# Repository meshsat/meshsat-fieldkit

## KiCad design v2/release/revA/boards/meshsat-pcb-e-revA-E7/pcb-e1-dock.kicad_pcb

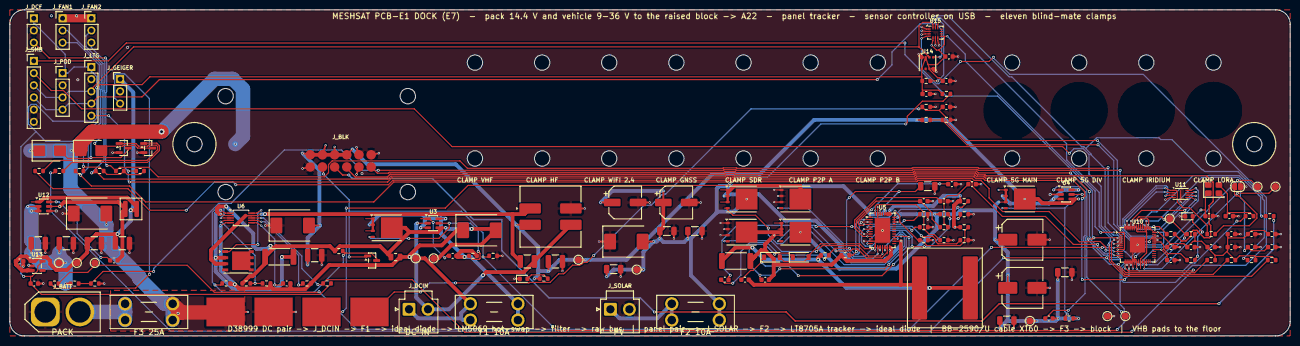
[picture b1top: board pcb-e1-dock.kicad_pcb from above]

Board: 4 copper layers, 267.0 x 68.0 mm, 189 parts (0 on the bottom side), 94 nets.

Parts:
C1, C31: 10u 25V 1210; C_1210_3225Metric
C2: 100n 100V; C_0805_2012Metric
C4, C28: 100n 50V; C_0603_1608Metric
C5: 100n (TIMER); C_0603_1608Metric
C6: 1u 100V 1210 (X, input side); C_1210_3225Metric
C7: 1u 100V 1210 (X, bus side); C_1210_3225Metric
C8: 10u 50V 1210; C_1210_3225Metric
C11, C12: 100u 35V Panasonic EEHZK1V101XP hybrid polymer (7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; CP_Elec_6.3x7.7
C13, C14: 10u 50V; C_1206_3216Metric
C15: 4.7u 50V; C_1206_3216Metric
C16: 1n; C_0603_1608Metric
C17, C18: 470n 25V; C_0603_1608Metric
C19: 4.7u 25V; C_1206_3216Metric
C20, C34, C35, C45, C46, C47: 1u; C_0603_1608Metric
C21: 4.7n; C_0603_1608Metric
C22: 100p; C_0603_1608Metric
C23, C30, C38, C39, C40, C41, C42, C43, C44, C48, C49, C50, C51: 100n; C_0603_1608Metric
C24, C25: 39u 35V Panasonic 35SVPF39M polymer (6.9 mm); CP_Elec_8x6.7
C26, C27: 10u 25V; C_1206_3216Metric
C32, C33: 22u 10V X7R 1210; C_1210_3225Metric
C36, C37: 15p; C_0603_1608Metric
D1: SMCJ33A (input surge, datasheet 50 V 100 ms); D_SMC
D2: SMCJ33A (bus clamp); D_SMC
D3: SMCJ18A (pack node clamp); D_SMC
D4: SMCJ33A (panel surge); D_SMC
D5: BAT54 boost diode INTVCC -> BOOST1; D_SOD-123
D6: BAT54 boost diode INTVCC -> BOOST2; D_SOD-123
D7: SS14 flyback across fan 1; D_SMB
D8: SS14 flyback across fan 2; D_SMB
F1: 10 A mini blade (Keystone 3568 holder): vehicle i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; Fuseholder_Blade_Mini_Keystone_3568
F2: 10 A mini blade (Keystone 3568 holder): panel inp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; Fuseholder_Blade_Mini_Keystone_3568
F3: 25 A mini blade (Keystone 3568 holder): pack to t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; Fuseholder_Blade_Mini_Keystone_3568
H1, H2: M3 rod pass-through, PCB-A standoff stands here; MountingHole_3.2mm_M3
H3, H4, H5, H6: M3 standoff, raised block; MountingHole_3.2mm_M3
H7, H8: M3, float clamp VHF; MountingHole_3.2mm_M3
H9, H10: M3, float clamp HF; MountingHole_3.2mm_M3
H11, H12: M3, float clamp WIFI 2.4; MountingHole_3.2mm_M3
H13, H14: M3, float clamp GNSS; MountingHole_3.2mm_M3
H15, H16: M3, float clamp SDR; MountingHole_3.2mm_M3
H17, H18: M3, float clamp P2P A; MountingHole_3.2mm_M3
H19, H20: M3, float clamp P2P B; MountingHole_3.2mm_M3
H21, H22: M3, float clamp 5G MAIN; MountingHole_3.2mm_M3
H23, H24: M3, float clamp 5G DIV; MountingHole_3.2mm_M3
H25, H26: M3, float clamp IRIDIUM; MountingHole_3.2mm_M3
H27, H28: M3, float clamp LORA; MountingHole_3.2mm_M3
JP1: BOOTSEL: short while powering to enter the USB bo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; SolderJumper-2_P1.3mm_Open_RoundedPad1.0x1.5mm
J_BATT: Amass XT60-M: the BB-2590/U pack cable BTA-70762-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; AMASS_XT60-M_1x02_P7.20mm_Vertical
J_BLK: solder lands for the 12 signal wires to the block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; PogoTargets_2x6
J_DCF: DCF77 receiver module: 3.3 V, GND, pulse; PinHeader_1x03_P2.54mm_Vertical
J_DCIN: JST-VH socket, 10 A: vehicle and shore DC in 9 to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; JST_VH_B2P-VH_1x02_P3.96mm_Vertical
J_FAN1: mixer fan 1 under the plate (12 V class fan on th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; PinHeader_1x03_P2.54mm_Vertical
J_FAN2: mixer fan 2 under the plate (12 V class fan on th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; PinHeader_1x03_P2.54mm_Vertical
J_GEIGER: Geiger counter module (RadiationD-v1.1 class): 5 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; PinHeader_1x03_P2.54mm_Vertical
J_LTG: AS3935 lightning sensor module (CJMCU-3935 class)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; PinHeader_1x05_P2.54mm_Vertical
J_POD: outside sensor pod on the connector plate (M8 sea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; PinHeader_1x04_P2.54mm_Vertical
J_SMB: pack SMBus (XH or pin header): section A SDA SCL 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; PinHeader_1x06_P2.54mm_Vertical
J_SOLAR: JST-VH socket, 10 A: bare panel in (lead from the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; JST_VH_B2P-VH_1x02_P3.96mm_Vertical
L1: 10uH Coilcraft XAL1510-103MED (Isat 26 A, 10.0 mm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; L_Coilcraft_XAL1510-103
L2: Bourns SRF1260-4R7Y dual-winding choke (7.2 A per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; L_CommonModeChoke_Bourns_SRF1260
L3: 4.7uH XAL4030-472ME; L_Coilcraft_XAL4020-XXX
LED1: green: vehicle input present; LED_0603_1608Metric
LED2: status (GPIO25); LED_0603_1608Metric
PAD_W1: water electrode A (bare copper, +3.3 V through 1 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; SolderPad_8x6
PAD_W2: water electrode B (bare copper, to ADC0); SolderPad_8x6
P_CN: solder pad, 12 AWG wire to the block board return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; SolderPad_8x6
P_CP: solder pad, 12 AWG wire to the block board CELL+ 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; SolderPad_8x6
Q1, Q2: BSC039N06NS 60 V 3.9 mOhm N-FET (PG-TDSON-8: 1-3 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; TDSON-8-1
Q3: BSC028N06NS 60 V 2.8 mOhm N-FET, M1 buck top (TDS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; TDSON-8-1
Q4: BSC039N06NS 60 V N-FET, M2 buck bottom; TDSON-8-1
Q5: BSC028N06NS 60 V N-FET, M3 boost bottom; TDSON-8-1
Q6: BSC039N06NS 60 V N-FET, M4 boost top; TDSON-8-1
Q7: CSD19532Q5B 100 V N-FET (4.6 mOhm at VGS 6 V, Pow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; PowerPAK_SO-8_Single
Q8: 2N7002: SHORE_INHIBIT high pulls UVLO low = input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; SOT-23
Q9: 2N7002 fan 1 low-side switch (1 G, 2 S, 3 D); SOT-23
Q10: 2N7002 fan 2 low-side switch (1 G, 2 S, 3 D); SOT-23
R1, R18, R26: 100k; R_0603_1608Metric
R5: 5 mOhm 1% 3 W 2512 RSENSE (RALEC LR2512-23R005F4); R_2512_6332Metric
R6, R7, R44, R45: 100R; R_0603_1608Metric
R8: 102k 1% (RFBIN1: panel point 17.6 V); R_0603_1608Metric
R9: 7.50k 1% (RFBIN2); R_0603_1608Metric
R10: 115k 1% (RFBOUT1: 15.1 V); R_0603_1608Metric
R11: 10.0k 1% (RFBOUT2); R_0603_1608Metric
R12: 215k 1% (RT: 202 kHz); R_0603_1608Metric
R13, R16, R17, R25, R31, R46, R47, R49, R50: 10k; R_0603_1608Metric
R14, R20, R22, R40, R42: 100k 1%; R_0603_1608Metric
R15: 15.0k 1% (SHDN: enable above about 9.5 V); R_0603_1608Metric
R19: 10mOhm 1% 2512 (hot-swap sense); R_2512_6332Metric
R21: 38.3k 1% (UVLO: 9 V); R_0603_1608Metric
R23: 6.65k 1% (OVLO: 40 V); R_0603_1608Metric
R24: 20k (PWR: power limit); R_0603_1608Metric
R27: 2.2k; R_0603_1608Metric
R28, R33: 1k; R_0603_1608Metric
R29, R30: 27R; R_0603_1608Metric
R32: 1k (BOOTSEL); R_0603_1608Metric
R34, R35, R36, R37: 4.7k; R_0603_1608Metric
R38, R39: 1M; R_0603_1608Metric
R41: 10k 1% (ADC1: 0.091 x bus); R_0603_1608Metric
R43: 22k 1% (ADC2: 0.18 x pack); R_0603_1608Metric
R48: 22R (pulse input series); R_0603_1608Metric
R51: 0R (CSB high: I2C mode; its own net keeps the pin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; R_0603_1608Metric
TP1: DC_IN; TestPoint_Pad_D1.5mm
TP2: DC_P; TestPoint_Pad_D1.5mm
TP3: VIN_RAW; TestPoint_Pad_D1.5mm
TP4: GND; TestPoint_Pad_D1.5mm
TP5: PV_P; TestPoint_Pad_D1.5mm
TP6: TRK_OUT; TestPoint_Pad_D1.5mm
TP7: BLK_SPARE; TestPoint_Pad_D1.5mm
TP8: CELL_F; TestPoint_Pad_D1.5mm
TP9: +5V_E6; TestPoint_Pad_D1.5mm
TP10: SWCLK; TestPoint_Pad_D1.5mm
TP11: SWDIO; TestPoint_Pad_D1.5mm
TP12: E6_RUN; TestPoint_Pad_D1.5mm
TP13: GEIGER_IN; TestPoint_Pad_D1.5mm
U3, U4: LM74700-Q1 ideal-diode controller: 1 VCAP 2 GND 3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; SOT-23-6
U5: LT8705A buck-boost controller, 38-lead QFN 5x7 (p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; WQFN-38-1EP_5x7mm_P0.5mm_EP3.15x5.15mm
U6: LM5069MM-2 hot-swap controller: 9 V on, 40 V off,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; VSSOP-10_3x3mm_P0.5mm
U10: RP2040 sensor controller (USB to B16 through the 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; QFN-56-1EP_7x7mm_P0.4mm_EP3.2x3.2mm
U11: W25Q16JVUXIQ 16 Mbit QSPI flash (USON-8: 1 CS 2 D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; Winbond_USON-8-1EP_3x2mm_P0.5mm_EP0.2x1.6mm
U12: AP63205WU-7 5 V 2 A buck for the controller, the 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; TSOT-23-6
U13: TLV75533PDBVR 3.3 V LDO; SOT-23-5
U14: BME688 inside climate: temperature, humidity, pre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; Bosch_LGA-8_3x3mm_P0.8mm_ClockwisePinNumbering
U15: BMI270 six-axis IMU (I2C 0x68): shock and tilt lo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; Bosch_LGA-14_3x2.5mm_P0.5mm
Y1: 12 MHz ABM8-272-T3 (3225): 1 XIN, 3 XOUT, 2 and 4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; Crystal_SMD_3225-4Pin_3.2x2.5mm

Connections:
/+3V3_E6: C35.1, C38.1, C39.1, C40.1, C41.1, C42.1, C43.1, C44.1, C47.1, C48.1, C49.1, C50.1, J_DCF.1, J_LTG.1, J_POD.1, R25.2, R31.2, R34.2, R35.2, R36.2, R37.2, R38.1, R46.2, R47.2, R49.2, R50.2, R51.1, U10.1, U10.10, U10.22, U10.33, U10.42, U10.43, U10.44, U10.48, U10.49, U11.8, U13.5, U14.2, U14.6, U14.8, U15.5, U15.8
/+5V_E6: C32.1, C33.1, C34.1, J_GEIGER.1, L3.2, TP9.1, U12.1, U13.1, U13.3
/BLK_SPARE: J_BLK.12, TP7.1
/BOOT_J: JP1.1, R32.2
/CELL+: F3.1, J_BATT.2
/CELL_F: C1.1, C31.1, D3.2, D7.1, D8.1, F3.2, J_FAN1.1, J_FAN2.1, P_CP.1, R42.1, TP8.1, U12.2, U12.3
/CELL_MON: R42.2, R43.1, U10.40
/DCF_PULSE: J_DCF.3, R49.1, U10.8
/DCIN_PGD: R25.1, U6.8, U10.15
/DC_F: C4.2, F1.2, Q1.1, Q1.2, Q1.3, R1.2, U3.3, U3.6
/DC_HS: C6.1, L2.1, Q7.3, U6.9
/DC_IN: F1.1, J_DCIN.1, TP1.1
/DC_P: C2.1, D1.2, Q1.5, R19.1, R20.1, R22.1, TP2.1, U3.4, U6.2
/E6_BST: C30.1, U12.6
/E6_DVDD: C45.1, C46.1, U10.23, U10.45, U10.50
/E6_RUN: R31.1, TP12.1, U10.26
/E6_SW: C30.2, L3.1, U12.5
/FAN1_G: Q9.1, R44.2
/FAN1_PWM: R44.1, U10.11
/FAN1_SW: D7.2, J_FAN1.2, Q9.3
/FAN1_TACH: J_FAN1.3, R46.1, U10.13
/FAN2_G: Q10.1, R45.2
/FAN2_PWM: R45.1, U10.12
/FAN2_SW: D8.2, J_FAN2.2, Q10.3
/FAN2_TACH: J_FAN2.3, R47.1, U10.14
/GEIGER_IN: R48.2, TP13.1, U10.9
/GEIGER_PULSE: J_GEIGER.3, R48.1
/GND_V: C2.2, C5.2, C6.2, D1.1, J_DCIN.2, L2.3, Q8.2, R21.2, R23.2, R24.2, U3.2, U6.5
/HS_GATE: Q7.1, U6.10
/HS_OVLO: R22.2, R23.1, U6.4
/HS_PWR: R24.1, U6.7
/HS_S: Q7.2, R19.2, U6.1
/HS_TIMER: C5.1, U6.6
/HS_UVLO: Q8.3, R20.2, R21.1, U6.3
/IMU_CSB: R51.2, U15.12
/IMU_INT1: U10.16, U15.4
/LED_A: LED1.2, R27.2
/LED_STAT: R33.1, U10.37
/LED_STAT_A: LED2.2, R33.2
/LTG_IRQ: J_LTG.5, R50.1, U10.17
/PV_IN: F2.1, J_SOLAR.1
/PV_P: C11.1, C12.1, C13.1, C14.1, C15.1, D4.2, F2.2, Q3.5, R8.1, R14.1, TP5.1, U5.32, U5.33, U5.34
/Q1_G: Q1.4, R1.1, U3.5
/Q2_G: Q2.4, R18.1, U4.5
/QSPI_D0: U10.53, U11.5
/QSPI_D1: U10.55, U11.2
/QSPI_D2: U10.54, U11.3
/QSPI_D3: U10.51, U11.7
/QSPI_SCLK: U10.52, U11.6
/QSPI_SS: R32.1, U10.56, U11.1
/SCL0: J_SMB.2, R35.1, U10.5
/SCL1: J_LTG.4, J_POD.4, J_SMB.4, R37.1, U10.7, U14.4, U15.13
/SDA0: J_SMB.1, R34.1, U10.4
/SDA1: J_LTG.3, J_POD.3, J_SMB.3, R36.1, U10.6, U14.3, U15.14
/SHORE_INHIBIT: J_BLK.8, Q8.1, R26.1, U10.18
/SWCLK: TP10.1, U10.24
/SWDIO: TP11.1, U10.25
/TRK_BG1: Q4.4, U5.14
/TRK_BG2: Q5.4, U5.16
/TRK_BOOST1: C17.1, D5.1, U5.23
/TRK_BOOST2: C18.1, D6.1, U5.17
/TRK_CSN: C16.2, R7.2, U5.2
/TRK_CSP: C16.1, R6.2, U5.3
/TRK_FBIN: R8.2, R9.1, U5.5
/TRK_FBOUT: R10.2, R11.1, U5.6
/TRK_IMONI: R16.1, U5.38
/TRK_IMONO: R17.1, U5.7
/TRK_INTVCC: C19.1, D5.2, D6.2, U5.15, U5.35, U5.36
/TRK_LDO33: C20.1, U5.4
/TRK_LSENSE: L1.2, R5.1, R6.1
/TRK_OUT: C24.1, C25.1, C26.1, C27.1, C28.2, Q2.1, Q2.2, Q2.3, Q6.5, R10.1, R18.2, TP6.1, U4.3, U4.6, U5.29, U5.30, U5.31
/TRK_RT: R12.1, U5.12
/TRK_SHDN: R14.2, R15.1, U5.1
/TRK_SS: C23.1, U5.9
/TRK_SW1: C17.2, L1.1, Q3.1, Q3.2, Q3.3, Q4.5, U5.21
/TRK_SW2: C18.2, Q5.5, Q6.1, Q6.2, Q6.3, R5.2, R7.1, U5.19
/TRK_TG1: Q3.4, U5.22
/TRK_TG2: Q6.4, U5.18
/TRK_VC: C22.1, R13.1, U5.8
/TRK_VCC1: C21.1, R13.2
/U3_VCAP: C4.1, U3.1
/U4_VCAP: C28.1, U4.1
/USB_DM_R: R30.1, U10.46
/USB_DP_R: R29.1, U10.47
/USB_E6_N: J_BLK.10, R30.2
/USB_E6_P: J_BLK.9, R29.2
/VIN_MON: R40.2, R41.1, U10.39
/VIN_RAW: C7.1, C8.1, D2.2, J_BLK.1, J_BLK.2, J_BLK.3, J_BLK.4, L2.2, Q2.5, R27.1, R40.1, TP3.1, U4.4
/WATER_A: PAD_W1.1, R38.2
/WATER_SENSE: C51.1, PAD_W2.1, R39.1, U10.38
/XIN: C36.1, U10.20, Y1.1
/XOUT: C37.1, R28.2, Y1.3
/XOUT_R: R28.1, U10.21
GND: C1.2, C7.2, C8.2, C11.2, C12.2, C13.2, C14.2, C15.2, C19.2, C20.2, C21.2, C22.2, C23.2, C24.2, C25.2, C26.2, C27.2, C31.2, C32.2, C33.2, C34.2, C35.2, C36.2, C37.2, C38.2, C39.2, C40.2, C41.2, C42.2, C43.2, C44.2, C45.2, C46.2, C47.2, C48.2, C49.2, C50.2, C51.2, D2.1, D3.1, D4.1, JP1.2, J_BATT.1, J_BLK.5, J_BLK.6, J_BLK.7, J_BLK.11, J_DCF.2, J_GEIGER.2, J_LTG.2, J_POD.2, J_SMB.5, J_SMB.6, J_SOLAR.2, L2.4, LED1.1, LED2.1, P_CN.1, Q4.1, Q4.2, Q4.3, Q5.1, Q5.2, Q5.3, Q9.2, Q10.2, R9.2, R11.2, R12.2, R15.2, R16.2, R17.2, R26.2, R39.2, R41.2, R43.2, TP4.1, U4.2, U5.11, U5.13, U5.37, U5.39, U10.19, U10.57, U11.4, U11.9, U12.4, U13.2, U14.1, U14.5, U14.7, U15.1, U15.2, U15.3, U15.6, U15.7, Y1.2, Y1.4

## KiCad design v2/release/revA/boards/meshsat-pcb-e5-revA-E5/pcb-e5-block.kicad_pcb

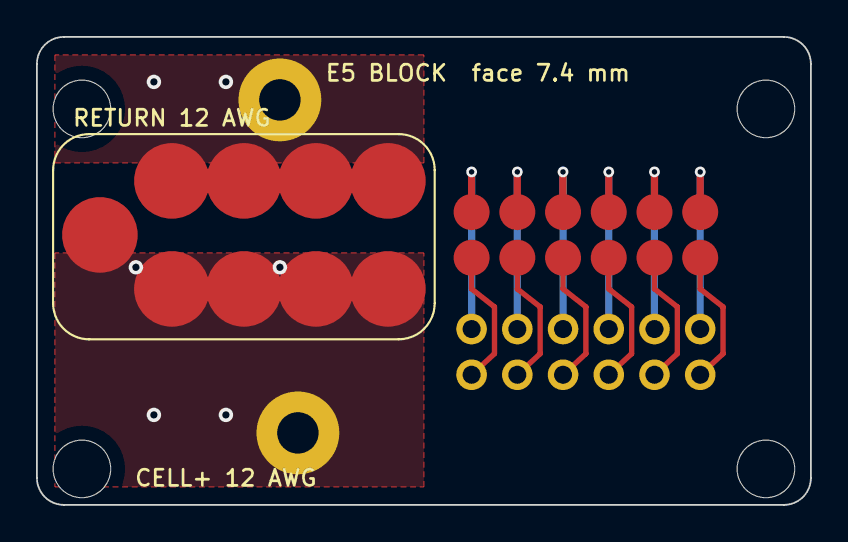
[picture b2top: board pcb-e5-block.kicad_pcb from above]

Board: 2 copper layers, 43.0 x 26.0 mm, 17 parts (0 on the bottom side), 14 nets.

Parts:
H1, H2, H3, H4: M3 standoff 6 mm to the dock strip; MountingHole_3.2mm_M3
L_SIG: plated wire lands to the strip J_BLK (net names o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; WireLands_2x6
T_CN1, T_CN2, T_CN3, T_CN4: return target (9 A pin); Mill-Max_0858_target
T_CP1, T_CP2, T_CP3, T_CP4: CELL+ target (9 A pin); Mill-Max_0858_target
T_PRE: pre-charge target (longer pin, mates first); Mill-Max_0858_target
T_SIG: signal targets (A22 J_DOCK lands here); PogoTargets_2x6
WH_CN: 12 AWG to the strip P_CN; WireHole_2mm
WH_CP: 12 AWG to the strip P_CP; WireHole_2mm

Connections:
CELL+: T_CP1.1, T_CP2.1, T_CP3.1, T_CP4.1, T_PRE.1, WH_CP.1
CELL_N: T_CN1.1, T_CN2.1, T_CN3.1, T_CN4.1, WH_CN.1
DOCK_SPARE_P12: L_SIG.6, T_SIG.6
GND_P5: L_SIG.11, T_SIG.11
GND_P6: L_SIG.12, T_SIG.12
GND_P7: L_SIG.1, T_SIG.1
GND_P11: L_SIG.5, T_SIG.5
SHORE_INHIBIT_P8: L_SIG.2, T_SIG.2
USB_E6_N_P10: L_SIG.4, T_SIG.4
USB_E6_P_P9: L_SIG.3, T_SIG.3
VIN_RAW_P1: L_SIG.7, T_SIG.7
VIN_RAW_P2: L_SIG.8, T_SIG.8
VIN_RAW_P3: L_SIG.9, T_SIG.9
VIN_RAW_P4: L_SIG.10, T_SIG.10

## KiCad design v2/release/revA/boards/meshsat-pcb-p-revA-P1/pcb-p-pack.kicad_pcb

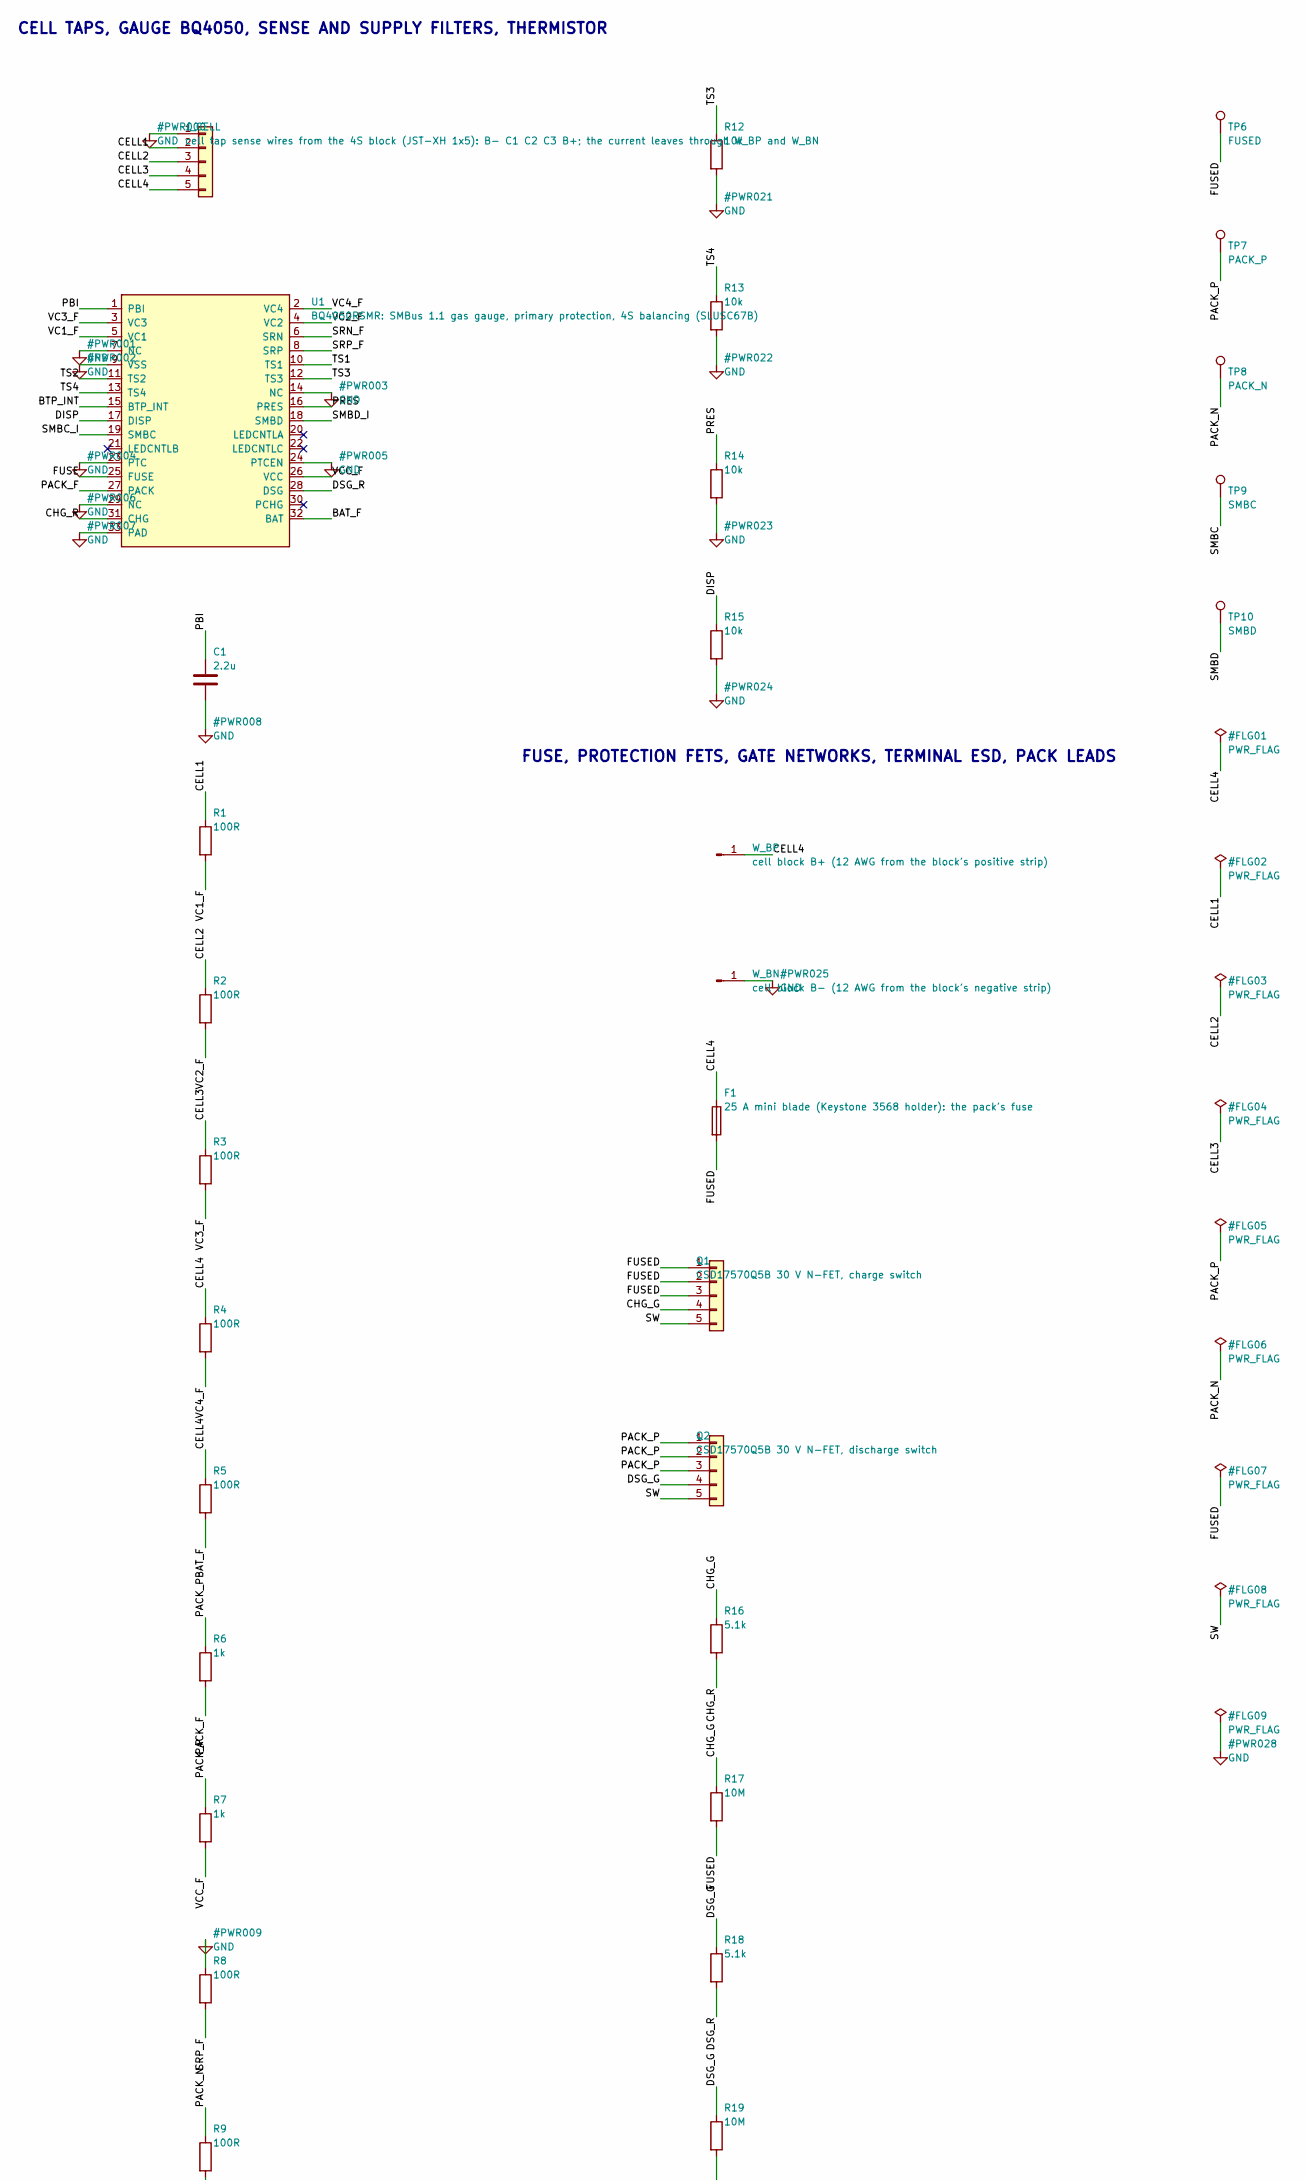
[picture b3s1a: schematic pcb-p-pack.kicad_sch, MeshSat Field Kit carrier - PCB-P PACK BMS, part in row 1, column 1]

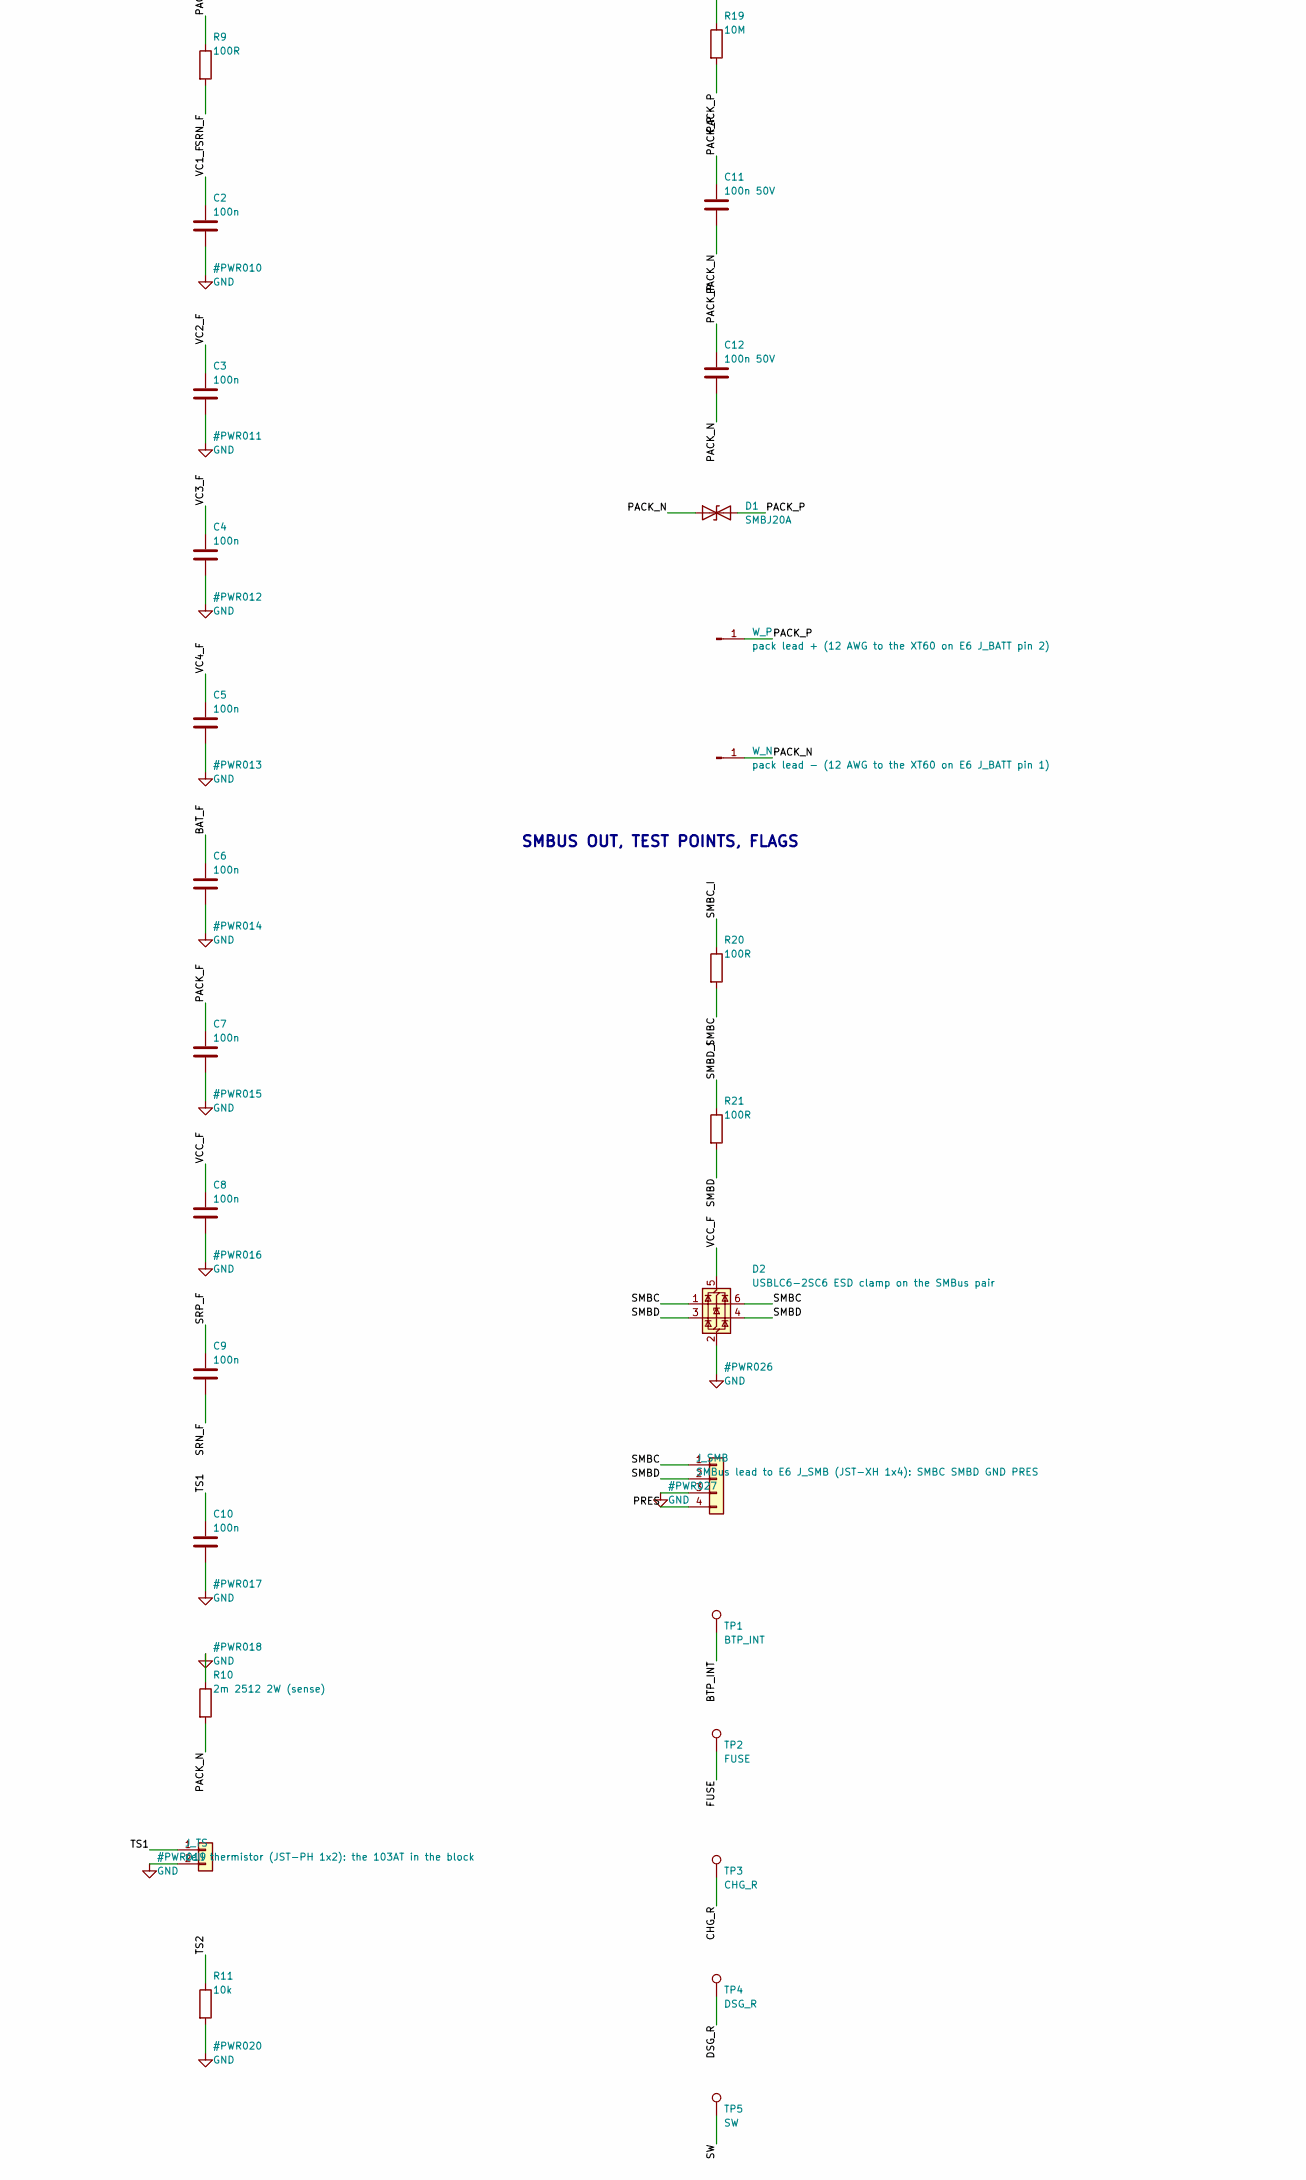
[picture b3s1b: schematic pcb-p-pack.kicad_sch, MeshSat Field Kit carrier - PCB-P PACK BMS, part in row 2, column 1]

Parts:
C1: 2.2u; C_0805_2012Metric
C2, C3, C4, C5, C6, C7, C8, C9, C10: 100n; C_0603_1608Metric
C11: 100n 50V; C_0603_1608Metric
C12: 100n 50V; C_1206_3216Metric
D1: SMBJ20A; D_SMB
D2: USBLC6-2SC6 ESD clamp on the SMBus pair; SOT-23-6; LCSC C7519
F1: 25 A mini blade (Keystone 3568 holder): the pack'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; Fuseholder_Blade_Mini_Keystone_3568
J_CELL: cell tap sense wires from the 4S block (JST-XH 1x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; JST_XH_B5B-XH-A_1x05_P2.50mm_Vertical
J_SMB: SMBus lead to E6 J_SMB (JST-XH 1x4): SMBC SMBD GN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; JST_XH_B4B-XH-A_1x04_P2.50mm_Vertical
J_TS: cell thermistor (JST-PH 1x2): the 103AT in the bl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; JST_PH_B2B-PH-K_1x02_P2.00mm_Vertical
Q1: CSD17570Q5B 30 V N-FET, charge switch; PowerPAK_SO-8_Single; LCSC C2825431
Q2: CSD17570Q5B 30 V N-FET, discharge switch; PowerPAK_SO-8_Single; LCSC C2825431
R1, R2, R3, R4, R5, R8, R9, R20, R21: 100R; R_0603_1608Metric
R6, R7: 1k; R_0603_1608Metric
R10: 2m 2512 2W (sense); R_2512_6332Metric
R11, R12, R13, R14, R15: 10k; R_0603_1608Metric
R16, R18: 5.1k; R_0603_1608Metric
R17, R19: 10M; R_0603_1608Metric
TP1: BTP_INT; TestPoint_Pad_D1.5mm
TP2: FUSE; TestPoint_Pad_D1.5mm
TP3: CHG_R; TestPoint_Pad_D1.5mm
TP4: DSG_R; TestPoint_Pad_D1.5mm
TP5: SW; TestPoint_Pad_D1.5mm
TP6: FUSED; TestPoint_Pad_D1.5mm
TP7: PACK_P; TestPoint_Pad_D1.5mm
TP8: PACK_N; TestPoint_Pad_D1.5mm
TP9: SMBC; TestPoint_Pad_D1.5mm
TP10: SMBD; TestPoint_Pad_D1.5mm
U1: BQ4050RSMR: SMBus 1.1 gas gauge, primary protecti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; QFN-32-1EP_5x5mm_P0.5mm_EP3.1x3.1mm; LCSC C157570
W_BN: cell block B- (12 AWG from the block's negative s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; SolderWire-2.5sqmm_1x01_D2.4mm_OD3.6mm
W_BP: cell block B+ (12 AWG from the block's positive s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; SolderWire-2.5sqmm_1x01_D2.4mm_OD3.6mm
W_N: pack lead - (12 AWG to the XT60 on E6 J_BATT pin 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; SolderWire-2.5sqmm_1x01_D2.4mm_OD3.6mm
W_P: pack lead + (12 AWG to the XT60 on E6 J_BATT pin 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; SolderWire-2.5sqmm_1x01_D2.4mm_OD3.6mm

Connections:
/BAT_F: C6.1, R5.2, U1.32 (BAT)
/BTP_INT: TP1.1, U1.15 (BTP_INT)
/CELL1: J_CELL.2, R1.1
/CELL2: J_CELL.3, R2.1
/CELL3: J_CELL.4, R3.1
/CELL4: F1.1, J_CELL.5, R4.1, R5.1, W_BP.1
/CHG_G: Q1.4, R16.1, R17.1
/CHG_R: R16.2, TP3.1, U1.31 (CHG)
/DISP: R15.1, U1.17 (DISP)
/DSG_G: Q2.4, R18.1, R19.1
/DSG_R: R18.2, TP4.1, U1.28 (DSG)
/FUSE: TP2.1, U1.25 (FUSE)
/FUSED: F1.2, Q1.1, Q1.2, Q1.3, R17.2, TP6.1
/PACK_F: C7.1, R6.2, U1.27 (PACK)
/PACK_N: C11.2, C12.2, D1.1 (A1), R9.1, R10.2, TP8.1, W_N.1
/PACK_P: C11.1, C12.1, D1.2 (A2), Q2.1, Q2.2, Q2.3, R6.1, R7.1, R19.2, TP7.1, W_P.1
/PBI: C1.1, U1.1 (PBI)
/PRES: J_SMB.4, R14.1, U1.16 (PRES)
/SMBC: D2.1 (I/O1), D2.6 (I/O1), J_SMB.1, R20.2, TP9.1
/SMBC_I: R20.1, U1.19 (SMBC)
/SMBD: D2.3 (I/O2), D2.4 (I/O2), J_SMB.2, R21.2, TP10.1
/SMBD_I: R21.1, U1.18 (SMBD)
/SRN_F: C9.2, R9.2, U1.6 (SRN)
/SRP_F: C9.1, R8.2, U1.8 (SRP)
/SW: Q1.5, Q2.5, TP5.1
/TS1: C10.1, J_TS.1, U1.10 (TS1)
/TS2: R11.1, U1.11 (TS2)
/TS3: R12.1, U1.12 (TS3)
/TS4: R13.1, U1.13 (TS4)
/VC1_F: C2.1, R1.2, U1.5 (VC1)
/VC2_F: C3.1, R2.2, U1.4 (VC2)
/VC3_F: C4.1, R3.2, U1.3 (VC3)
/VC4_F: C5.1, R4.2, U1.2 (VC4)
/VCC_F: C8.1, D2.5 (VBUS), R7.2, U1.26 (VCC)
GND: C1.2, C2.2, C3.2, C4.2, C5.2, C6.2, C7.2, C8.2, C10.2, D2.2 (GND), J_CELL.1, J_SMB.3, J_TS.2, R8.1, R10.1, R11.2, R12.2, R13.2, R14.2, R15.2, U1.7 (NC), U1.9 (VSS), U1.14 (NC), U1.23 (PTC), U1.24 (PTCEN), U1.29 (NC), U1.33 (PAD), W_BN.1

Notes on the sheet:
CELL TAPS, GAUGE BQ4050, SENSE AND SUPPLY FILTERS, THERMISTOR
FUSE, PROTECTION FETS, GATE NETWORKS, TERMINAL ESD, PACK LEADS
SMBUS OUT, TEST POINTS, FLAGS

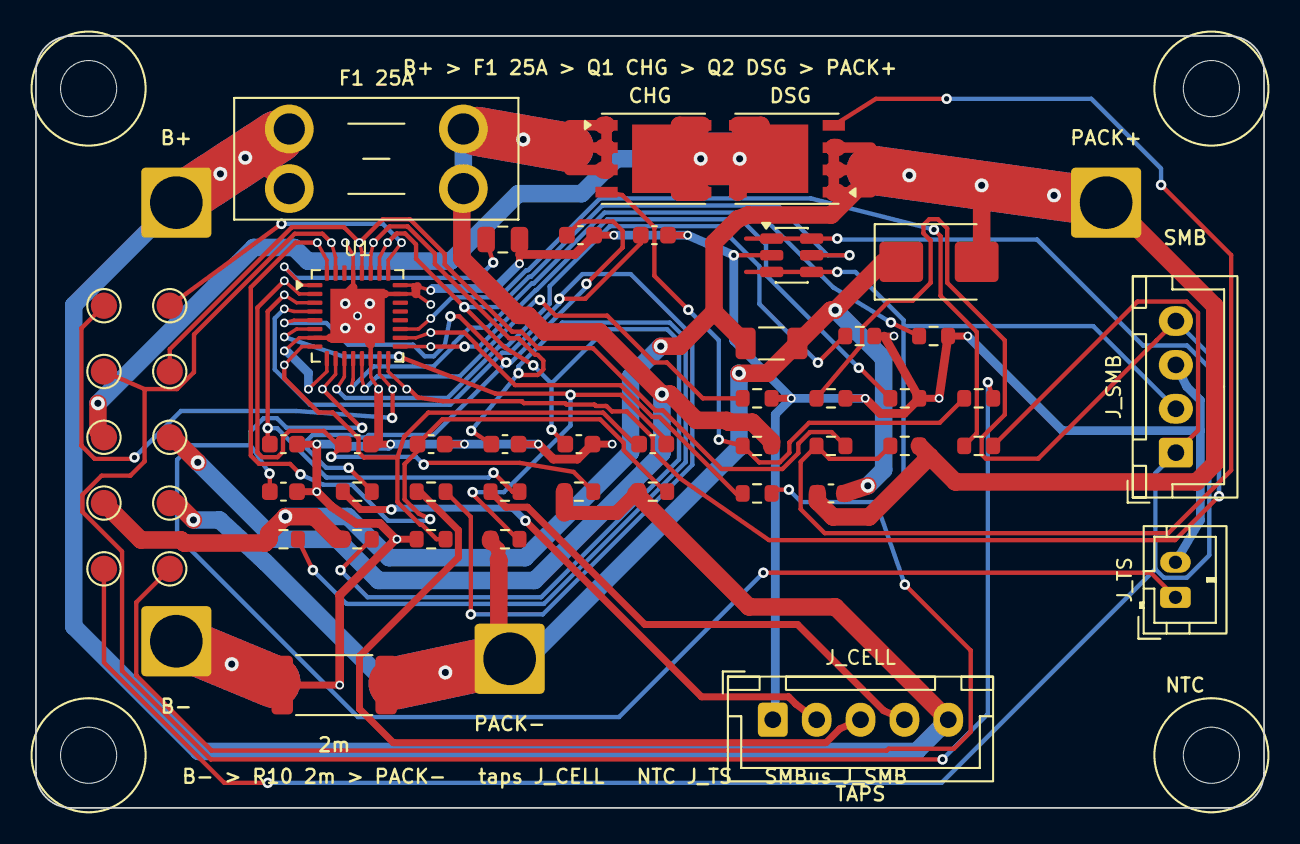
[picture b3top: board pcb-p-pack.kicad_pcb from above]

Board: 2 copper layers, 70.0 x 44.0 mm, 60 parts (0 on the bottom side), 35 nets.

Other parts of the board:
H1, H2, H3, H4: M3 into the enclosure boss; MountingHole_3.2mm_M3
